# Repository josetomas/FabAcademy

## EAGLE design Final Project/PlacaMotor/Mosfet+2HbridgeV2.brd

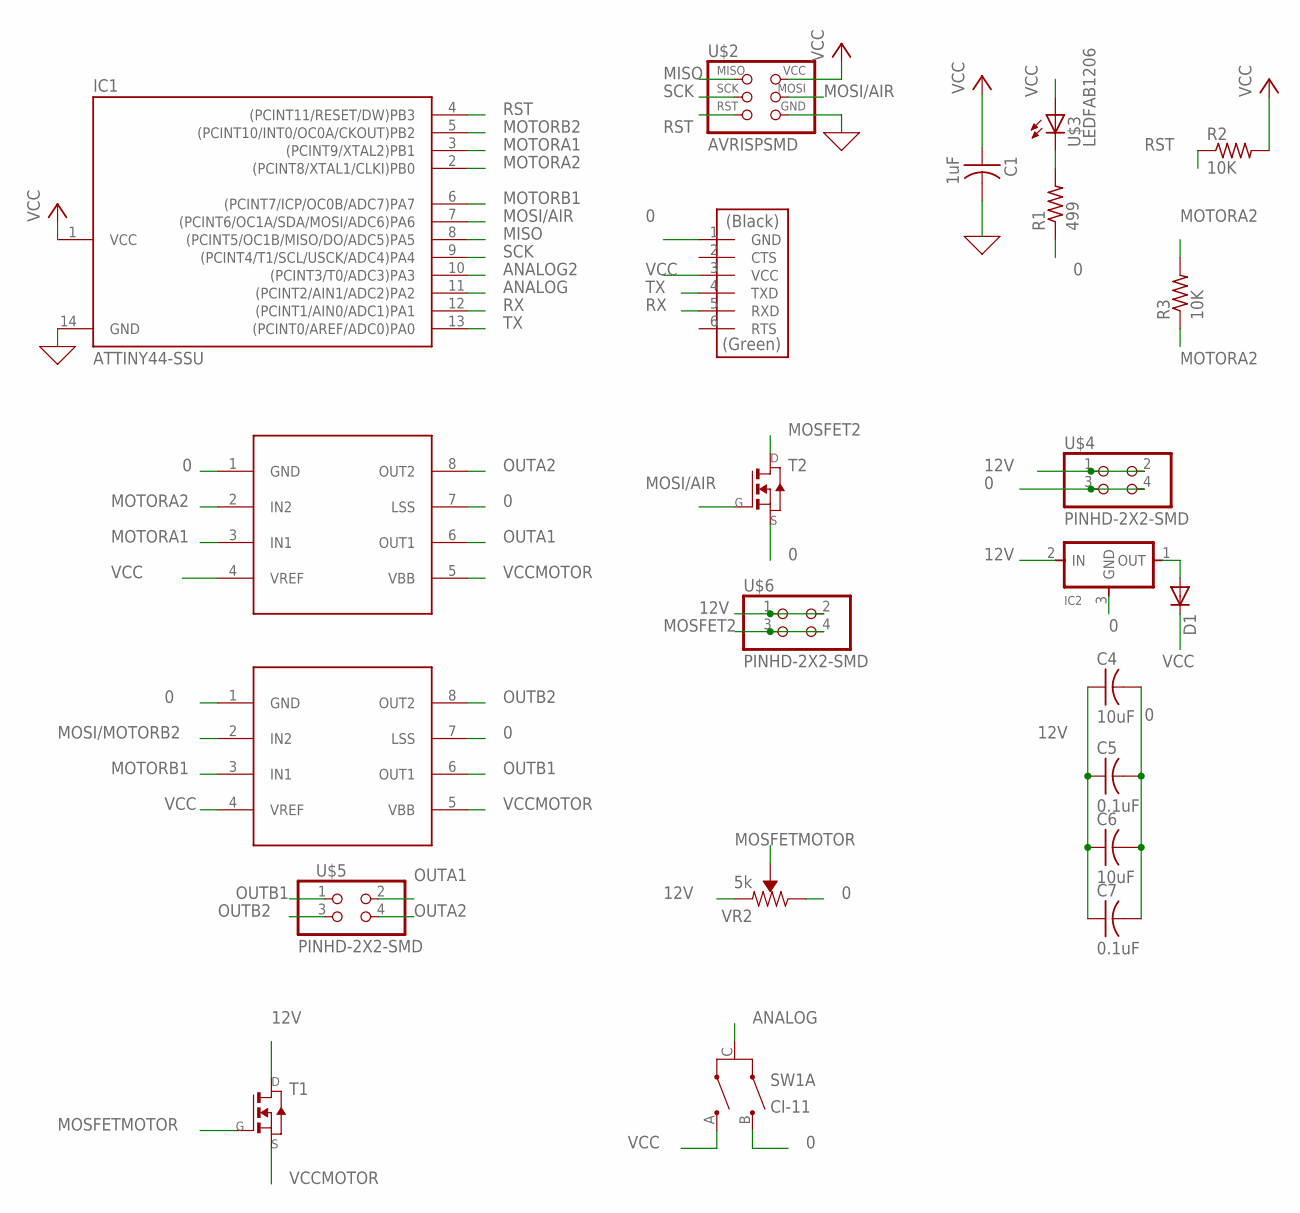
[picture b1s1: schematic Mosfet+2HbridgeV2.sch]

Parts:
C1: 1uF; C1206FAB
C4, C6: 10uF; C1206FAB
C5, C7: 0.1uF; C1206FAB
D1: DIODESOD123; SOD123
IC1: ATTINY44-SSU; SOIC14
IC2: REGULATORSOT23; SOT23
R1: 499; R1206FAB
R2, R3: 10K; R1206FAB
SW1: CI-11
T1, T2: NMOSFETSOT23; SOT-23
U$1: FTDI-SMD-HEADER; 1X06SMD
U$2: AVRISPSMD; 2X03SMD
U$3: LEDFAB1206; LED1206FAB
U$4, U$5, U$6: PINHD-2X2-SMD; 2X02SMD
U$7, U$8: A4953-H-BRIDGE-MOTOR-DRIVER; SOIC8
VR2: 5k; TRIMPOT-SMD-5MM

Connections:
0: C1.2, C4.2, C5.2, C6.2, C7.2, IC1.14 (GND), IC2.3 (GND), R1.1, SW1.B, T2.2 (S), U$1.1 (GND), U$2.6 (GND), U$4.3, U$4.4, U$7.1 (GND), U$7.7 (LSS), U$8.1 (GND), U$8.7 (LSS), VR2.C (CW)
12V: C4.1, C5.1, C6.1, C7.1, IC2.2 (IN), T1.1 (D), U$4.1, U$4.2, U$6.1, U$6.2, VR2.A (CCW)
ANALOG: IC1.11 ((PCINT2/AIN1/ADC2)PA2), SW1.C
ANALOG2: IC1.10 ((PCINT3/T0/ADC3)PA3)
MISO: IC1.8 ((PCINT5/OC1B/MISO/DO/ADC5)PA5), U$2.1 (MISO)
MOSFET2: T2.1 (D), U$6.3, U$6.4
MOSFETMOTOR: T1.3 (G), VR2.B (WIPER)
MOSI/AIR: IC1.7 ((PCINT6/OC1A/SDA/MOSI/ADC6)PA6), T2.3 (G), U$2.4 (MOSI)
MOSI/MOTORB2: U$7.2 (IN2)
MOTORA1: IC1.3 ((PCINT9/XTAL2)PB1), U$8.3 (IN1)
MOTORA2: IC1.2 ((PCINT8/XTAL1/CLKI)PB0), R3.1, R3.2, U$8.2 (IN2)
MOTORB1: IC1.6 ((PCINT7/ICP/OC0B/ADC7)PA7), U$7.3 (IN1)
MOTORB2: IC1.5 ((PCINT10/INT0/OC0A/CKOUT)PB2)
unnamed: R1.2, U$3.2 (C)
unnamed: D1.ANODE (A), IC2.1 (OUT)
OUTA1: U$5.2, U$8.6 (OUT1)
OUTA2: U$5.4, U$8.8 (OUT2)
OUTB1: U$5.1, U$7.6 (OUT1)
OUTB2: U$5.3, U$7.8 (OUT2)
RST: IC1.4 ((PCINT11/RESET/DW)PB3), R2.1, U$2.5 (RST)
RX: IC1.12 ((PCINT1/AIN0/ADC1)PA1), U$1.5 (RXD)
SCK: IC1.9 ((PCINT4/T1/SCL/USCK/ADC4)PA4), U$2.3 (SCK)
TX: IC1.13 ((PCINT0/AREF/ADC0)PA0), U$1.4 (TXD)
VCC: C1.1, D1.CATHODE (C), IC1.1 (VCC), R2.2, SW1.A, U$1.3 (VCC), U$2.2 (VCC), U$3.1 (A), U$7.4 (VREF), U$8.4 (VREF)
VCCMOTOR: T1.2 (S), U$7.5 (VBB), U$8.5 (VBB)

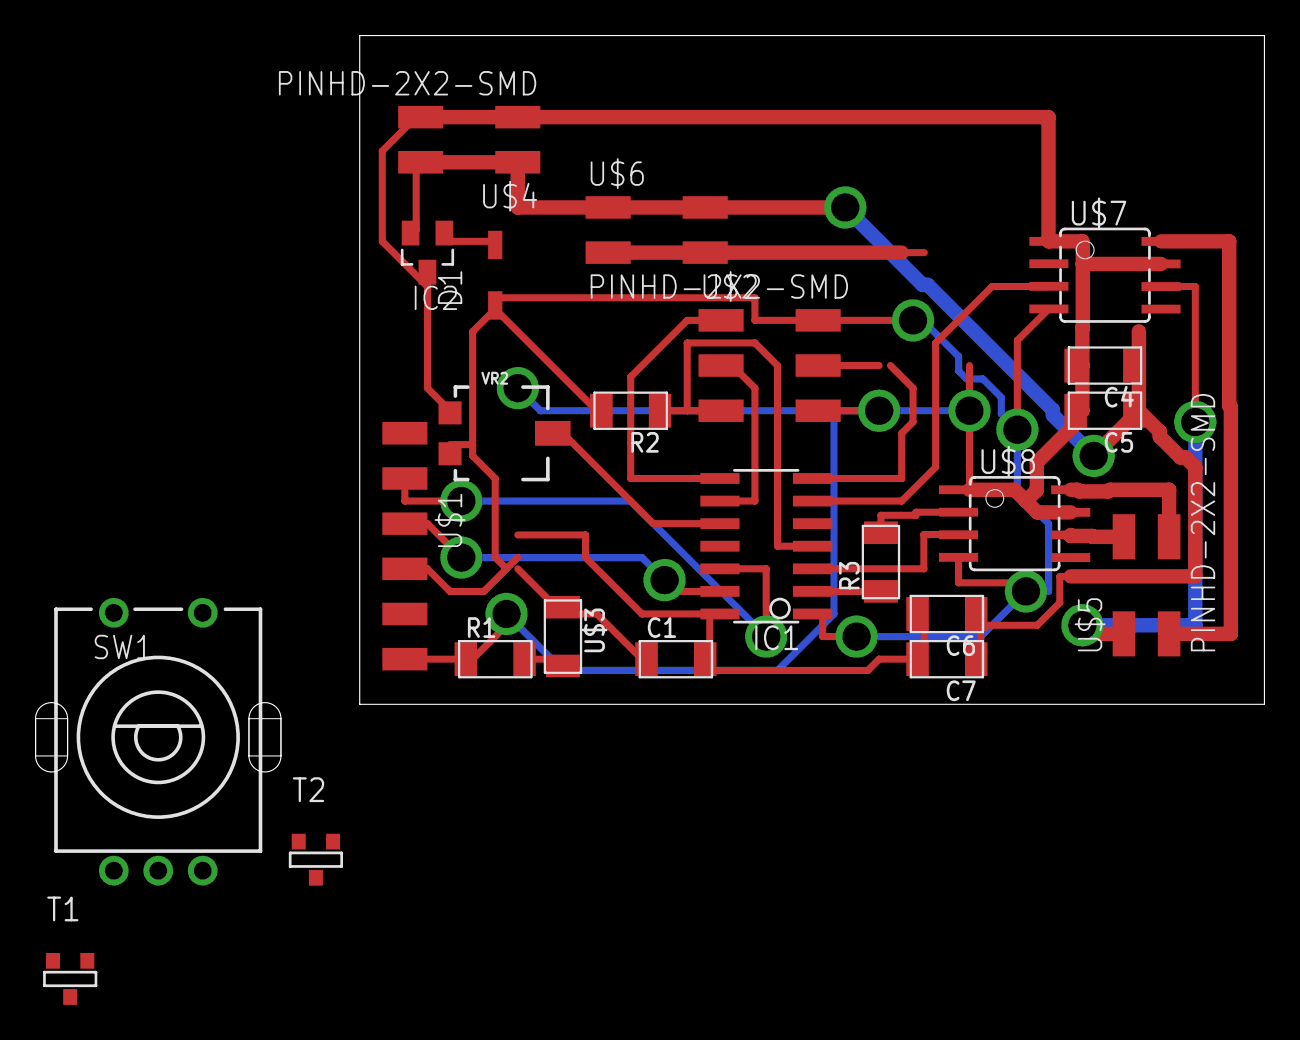
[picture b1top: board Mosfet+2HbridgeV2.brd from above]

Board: 2 copper layers, 50.9 x 37.6 mm, 23 parts (0 on the bottom side), 22 nets.

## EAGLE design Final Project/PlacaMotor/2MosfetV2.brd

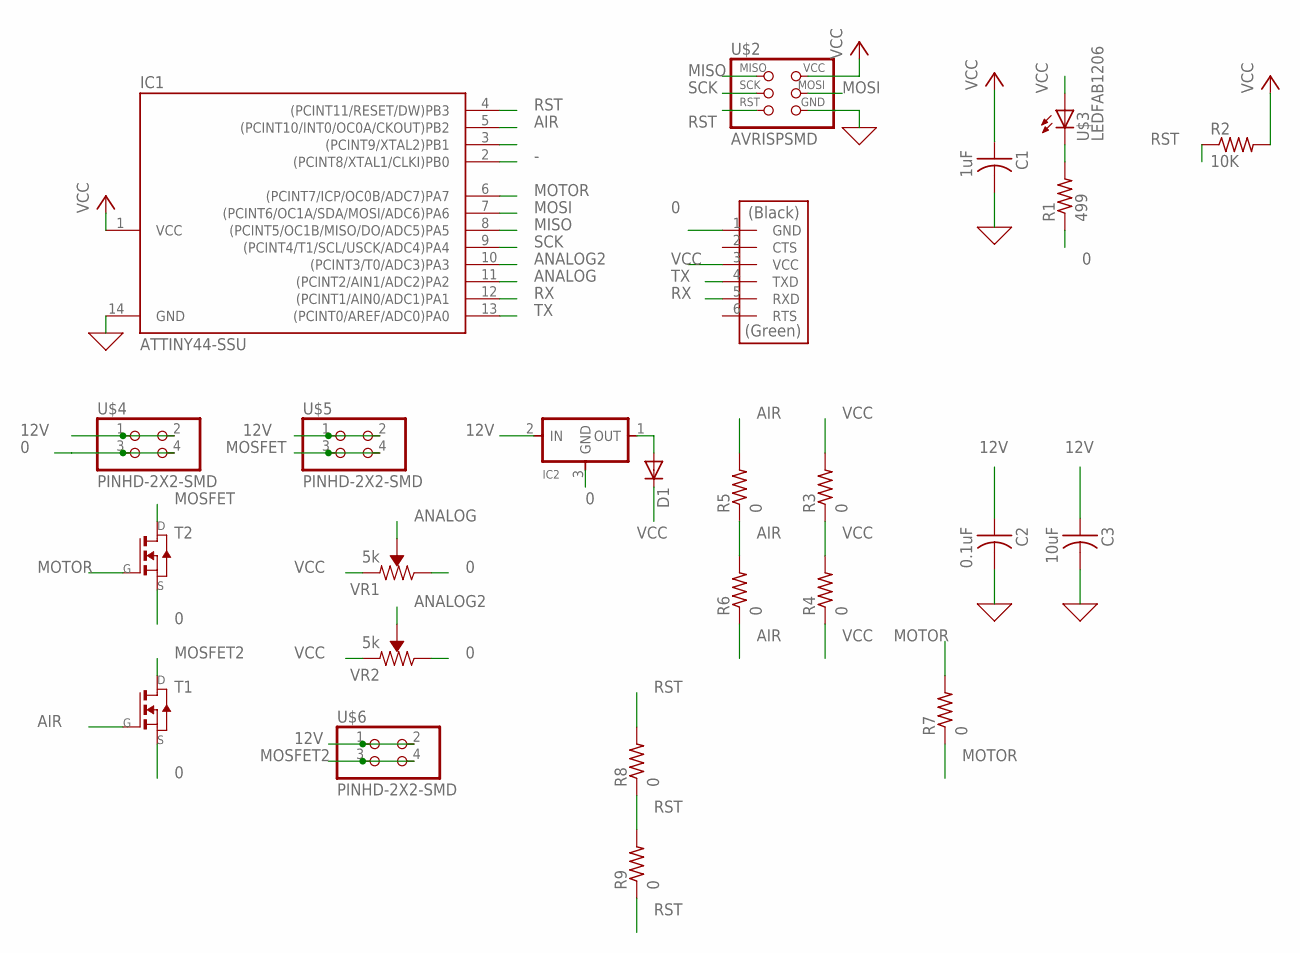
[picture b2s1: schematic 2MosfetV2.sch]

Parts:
C1: 1uF; C1206FAB
C2: 0.1uF; C1206FAB
C3: 10uF; C1206FAB
D1: DIODESOD123; SOD123
IC1: ATTINY44-SSU; SOIC14
IC2: REGULATORSOT23; SOT23
R1: 499; R1206FAB
R2: 10K; R1206FAB
R3, R4, R5, R6, R7, R8, R9: 0; R1206FAB
T1, T2: NMOSFETTO252; TO252
U$1: FTDI-SMD-HEADER; 1X06SMD
U$2: AVRISPSMD; 2X03SMD
U$3: LEDFAB1206; LED1206FAB
U$4, U$5, U$6: PINHD-2X2-SMD; 2X02SMD
VR1, VR2: 5k; TRIMPOT-SMD-5MM

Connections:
0: C1.2, C2.2, C3.2, IC1.14 (GND), IC2.3 (GND), R1.1, T1.2 (S), T2.2 (S), U$1.1 (GND), U$2.6 (GND), U$4.3, U$4.4, VR1.C (CW), VR2.C (CW)
12V: C2.1, C3.1, IC2.2 (IN), U$4.1, U$4.2, U$5.1, U$5.2, U$6.1, U$6.2
-: IC1.2 ((PCINT8/XTAL1/CLKI)PB0)
AIR: IC1.5 ((PCINT10/INT0/OC0A/CKOUT)PB2), R5.1, R5.2, R6.1, R6.2, T1.1 (G)
ANALOG: IC1.11 ((PCINT2/AIN1/ADC2)PA2), VR1.B (WIPER)
ANALOG2: IC1.10 ((PCINT3/T0/ADC3)PA3), VR2.B (WIPER)
MISO: IC1.8 ((PCINT5/OC1B/MISO/DO/ADC5)PA5), U$2.1 (MISO)
MOSFET: T2.3 (D), U$5.3, U$5.4
MOSFET2: T1.3 (D), U$6.3, U$6.4
MOSI: IC1.7 ((PCINT6/OC1A/SDA/MOSI/ADC6)PA6), U$2.4 (MOSI)
MOTOR: IC1.6 ((PCINT7/ICP/OC0B/ADC7)PA7), R7.1, R7.2, T2.1 (G)
unnamed: R1.2, U$3.2 (C)
unnamed: D1.ANODE (A), IC2.1 (OUT)
RST: IC1.4 ((PCINT11/RESET/DW)PB3), R2.1, R8.1, R8.2, R9.1, R9.2, U$2.5 (RST)
RX: IC1.12 ((PCINT1/AIN0/ADC1)PA1), U$1.5 (RXD)
SCK: IC1.9 ((PCINT4/T1/SCL/USCK/ADC4)PA4), U$2.3 (SCK)
TX: IC1.13 ((PCINT0/AREF/ADC0)PA0), U$1.4 (TXD)
VCC: C1.1, D1.CATHODE (C), IC1.1 (VCC), R2.2, R3.1, R3.2, R4.1, R4.2, U$1.3 (VCC), U$2.2 (VCC), U$3.1 (A), VR1.A (CCW), VR2.A (CCW)

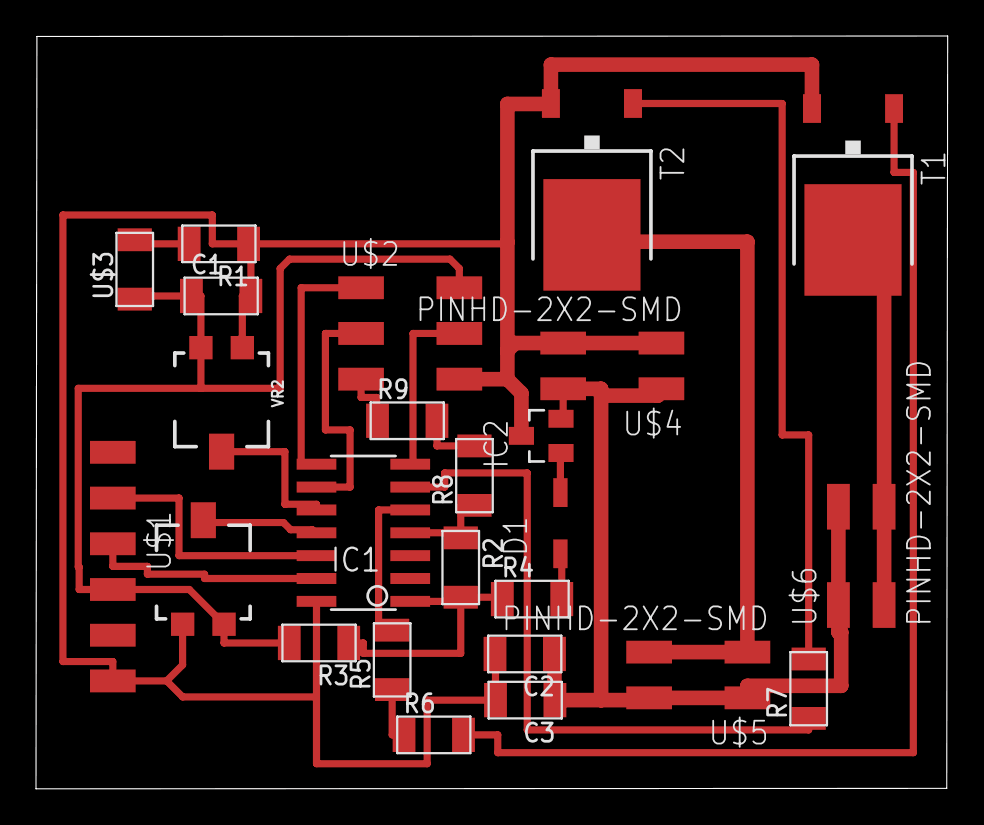
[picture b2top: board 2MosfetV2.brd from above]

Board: 2 copper layers, 50.6 x 41.8 mm, 25 parts (0 on the bottom side), 17 nets.

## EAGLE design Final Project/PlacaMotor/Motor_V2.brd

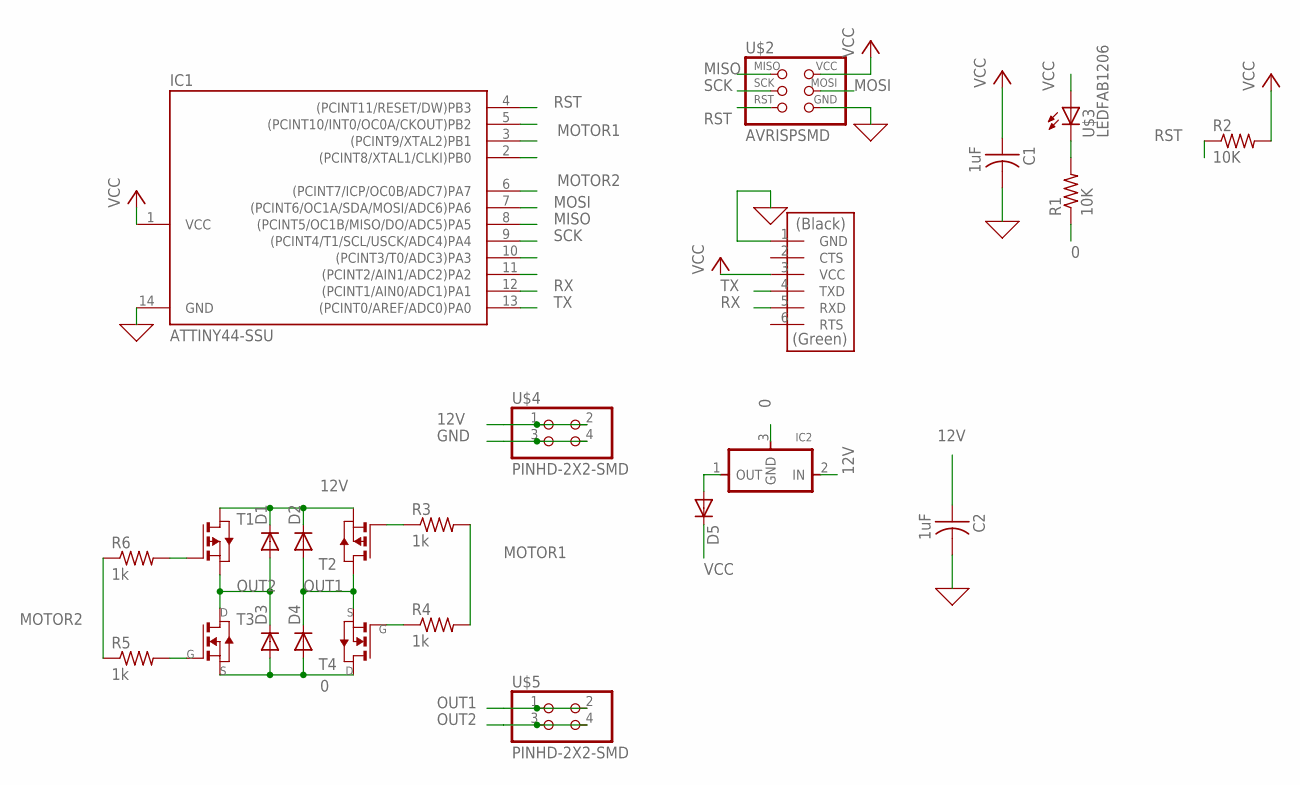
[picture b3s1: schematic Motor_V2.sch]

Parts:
C1, C2: 1uF; C1206FAB
D1, D2, D3, D4, D5: DIODESOD123; SOD123
IC1: ATTINY44-SSU; SOIC14
IC2: REGULATORSOT23; SOT23
R1, R2: 10K; R1206FAB
R3, R4, R5, R6: 1k; R1206FAB
T1, T2: PMOSFETSOT23; SOT-23
T3, T4: NMOSFETSOT23; SOT-23
U$1: FTDI-SMD-HEADER; 1X06SMD
U$2: AVRISPSMD; 2X03SMD
U$3: LEDFAB1206; LED1206FAB
U$4, U$5: PINHD-2X2-SMD; 2X02SMD

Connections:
0: C1.2, C2.2, D3.ANODE (A), D4.ANODE (A), IC1.14 (GND), IC2.3 (GND), R1.1, T3.2 (S), T4.1 (D), U$1.1 (GND), U$2.6 (GND)
12V: C2.1, D1.CATHODE (C), D2.CATHODE (C), IC2.2 (IN), T1.1 (D), T2.2 (S), U$4.1, U$4.2
GND: U$4.3, U$4.4
MISO: IC1.8 ((PCINT5/OC1B/MISO/DO/ADC5)PA5), U$2.1 (MISO)
MOSI: IC1.7 ((PCINT6/OC1A/SDA/MOSI/ADC6)PA6), U$2.4 (MOSI)
MOTOR1: IC1.5 ((PCINT10/INT0/OC0A/CKOUT)PB2), R3.2, R4.2
MOTOR2: IC1.6 ((PCINT7/ICP/OC0B/ADC7)PA7), R5.1, R6.1
unnamed: R1.2, U$3.2 (C)
unnamed: D5.ANODE (A), IC2.1 (OUT)
unnamed: R6.2, T1.3 (G)
unnamed: R5.2, T3.3 (G)
unnamed: R4.1, T4.3 (G)
unnamed: R3.1, T2.3 (G)
OUT1: D2.ANODE (A), D4.CATHODE (C), T2.1 (D), T4.2 (S), U$5.1, U$5.2
OUT2: D1.ANODE (A), D3.CATHODE (C), T1.2 (S), T3.1 (D), U$5.3, U$5.4
RST: IC1.4 ((PCINT11/RESET/DW)PB3), R2.1, U$2.5 (RST)
RX: IC1.12 ((PCINT1/AIN0/ADC1)PA1), U$1.5 (RXD)
SCK: IC1.9 ((PCINT4/T1/SCL/USCK/ADC4)PA4), U$2.3 (SCK)
TX: IC1.13 ((PCINT0/AREF/ADC0)PA0), U$1.4 (TXD)
VCC: C1.1, D5.CATHODE (C), IC1.1 (VCC), R2.2, U$1.3 (VCC), U$2.2 (VCC), U$3.1 (A)

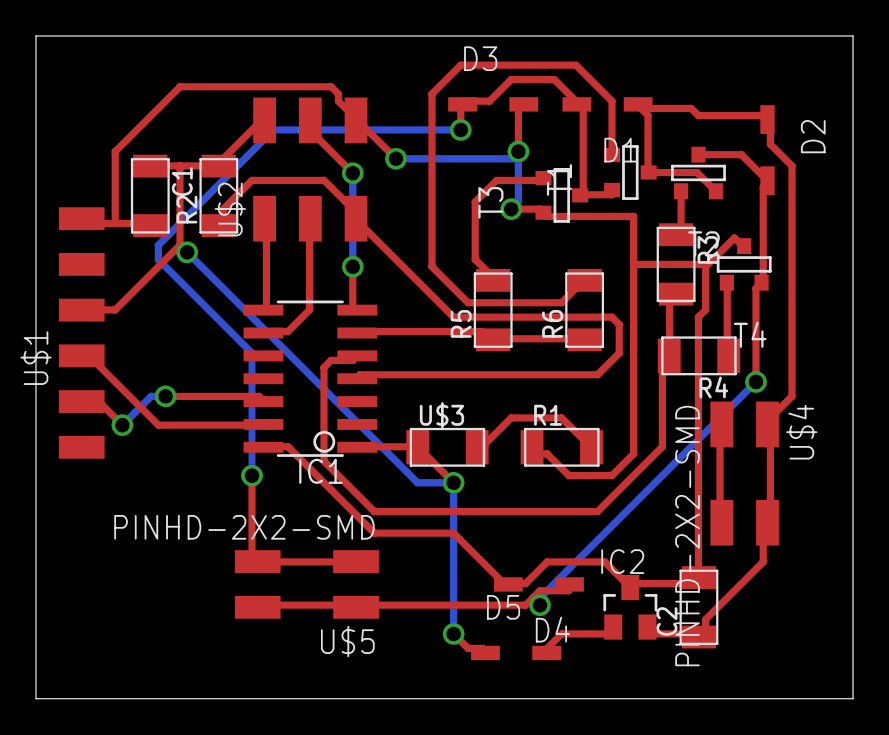
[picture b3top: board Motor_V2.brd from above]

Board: 2 copper layers, 45.4 x 36.8 mm, 24 parts (0 on the bottom side), 20 nets.

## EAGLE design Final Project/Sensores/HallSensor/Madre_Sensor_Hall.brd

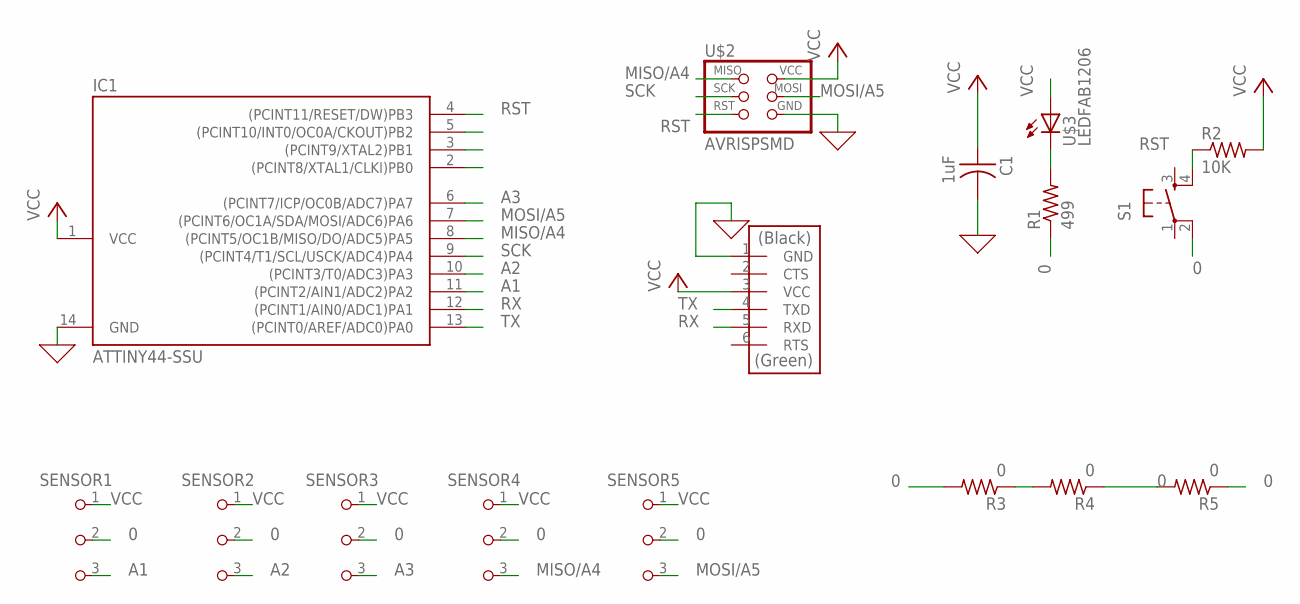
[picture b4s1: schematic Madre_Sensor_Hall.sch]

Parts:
C1: 1uF; C1206FAB
IC1: ATTINY44-SSU; SOIC14
R1: 499; R1206FAB
R2: 10K; R1206FAB
R3, R4, R5: 0; R1206FAB
S1: 6MM_SWITCH6MM_SWITCH; 6MM_SWITCH
SENSOR1, SENSOR2, SENSOR3, SENSOR4, SENSOR5: SPDTSWITCH
U$1: FTDI-SMD-HEADER; 1X06SMD
U$2: AVRISPSMD; 2X03SMD
U$3: LEDFAB1206; LED1206FAB

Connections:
0: C1.2, IC1.14 (GND), R1.1, R3.1, R3.2, R4.1, R4.2, R5.1, R5.2, S1.2 (P1), SENSOR1.2, SENSOR2.2, SENSOR3.2, SENSOR4.2, SENSOR5.2, U$1.1 (GND), U$2.6 (GND)
A1: IC1.11 ((PCINT2/AIN1/ADC2)PA2), SENSOR1.3
A2: IC1.10 ((PCINT3/T0/ADC3)PA3), SENSOR2.3
A3: IC1.6 ((PCINT7/ICP/OC0B/ADC7)PA7), SENSOR3.3
MISO/A4: IC1.8 ((PCINT5/OC1B/MISO/DO/ADC5)PA5), SENSOR4.3, U$2.1 (MISO)
MOSI/A5: IC1.7 ((PCINT6/OC1A/SDA/MOSI/ADC6)PA6), SENSOR5.3, U$2.4 (MOSI)
unnamed: R1.2, U$3.2 (C)
RST: IC1.4 ((PCINT11/RESET/DW)PB3), R2.1, S1.4 (S1), U$2.5 (RST)
RX: IC1.12 ((PCINT1/AIN0/ADC1)PA1), U$1.5 (RXD)
SCK: IC1.9 ((PCINT4/T1/SCL/USCK/ADC4)PA4), U$2.3 (SCK)
TX: IC1.13 ((PCINT0/AREF/ADC0)PA0), U$1.4 (TXD)
VCC: C1.1, IC1.1 (VCC), R2.2, SENSOR1.1, SENSOR2.1, SENSOR3.1, SENSOR4.1, SENSOR5.1, U$1.3 (VCC), U$2.2 (VCC), U$3.1 (A)

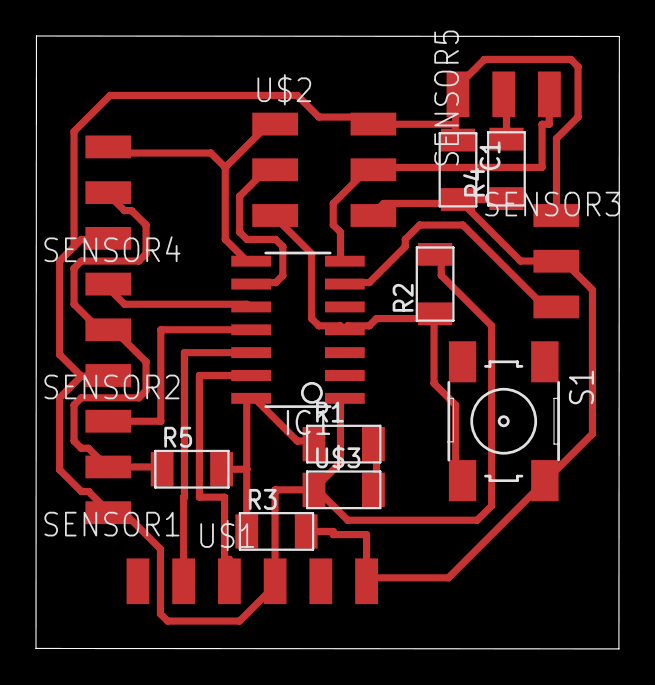
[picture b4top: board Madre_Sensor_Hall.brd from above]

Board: 2 copper layers, 32.4 x 34.1 mm, 16 parts (0 on the bottom side), 12 nets.

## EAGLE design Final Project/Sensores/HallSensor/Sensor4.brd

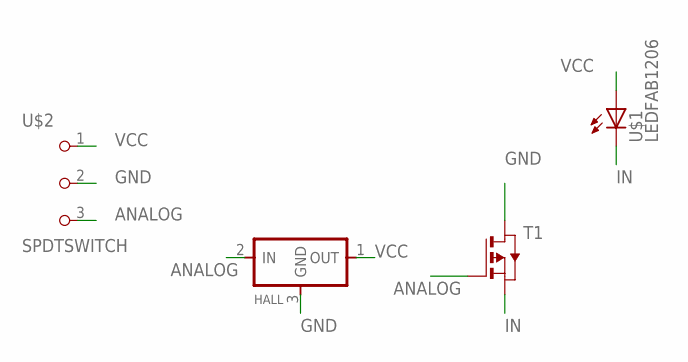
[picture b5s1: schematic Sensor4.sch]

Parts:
HALL: REGULATORSOT23; SOT23
T1: PMOSFETSOT23; SOT-23
U$1: LEDFAB1206; LED1206FAB
U$2: SPDTSWITCH

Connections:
ANALOG: HALL.2 (IN), T1.3 (G), U$2.3
GND: HALL.3 (GND), T1.1 (D), U$2.2
IN: T1.2 (S), U$1.2 (C)
VCC: HALL.1 (OUT), U$1.1 (A), U$2.1

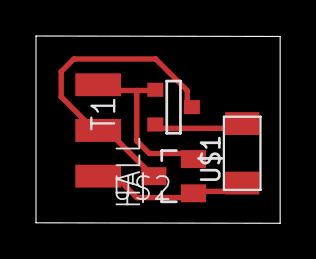
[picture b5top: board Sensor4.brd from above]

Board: 2 copper layers, 13.6 x 10.4 mm, 4 parts (0 on the bottom side), 4 nets.

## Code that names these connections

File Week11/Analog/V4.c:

#include <avr/io.h>
#include <util/delay.h>

#define output(directions,pin) (directions |= pin) // set port direction for output
#define set(port,pin) (port |= pin) // set port pin
#define clear(port,pin) (port &= (~pin)) // clear port pin
#define pin_test(pins,pin) (pins & pin) // test for port pin
#define bit_test(byte,bit) (byte & (1 << bit)) // test for bit set
#define bit_delay_time 102 // bit delay for 9600 with overhead
#define bit_delay() _delay_us(bit_delay_time) // RS232 bit delay
#define half_bit_delay() _delay_us(bit_delay_time/2) // RS232 half bit delay
#define charge_delay_1() _delay_us(1) // charge delay 1
#define charge_delay_2() _delay_us(10) // charge delay 2
#define charge_delay_3() _delay_us(100) // charge delay 3
#define settle_delay() _delay_us(100) // settle delay
#define char_delay() _delay_ms(10) // char delay

#define serial_port PORTA
#define serial_direction DDRA
#define serial_pin_out (1 << PA1)
#define charge_port PORTA
#define charge_direction DDRA
#define charge_pin1 (1 << PA7)
#define charge_pin2 (1 << PA5)
#define charge_pin3 (1<<PA4)


#define Sens1 0b00000011 //TX1@PA3
#define Sens2 0b00000010 //TX2@PA2
#define Sens3 0b00000000 //TX3@PA0

int Read_Sensor(uint8_t bit, unsigned char pin, unsigned char port){
	ADMUX |= bit;
	static unsigned char up_lo, up_hi, down_lo, down_hi;
	settle_delay();
   set(port, pin);
   charge_delay_1();
	ADCSRA |= (1<<ADSC);
	while (ADCSRA & (1<<ADSC))
      ;
   up_lo = ADCL;
   up_hi = ADCH;
   settle_delay();
   clear(port, pin);
   charge_delay_1();
   ADCSRA |= (1<<ADSC);
   while (ADCSRA & (1<<ADSC))
      ;
   down_lo = ADCL;
   down_hi = ADCH;

   int x = 256*up_hi+up_lo;
   int y=256*down_hi+down_lo;
   int z= x; 
   return z;

}

void put_char(volatile unsigned char *port, unsigned char pin, char txchar) {
   //
   // send character in txchar on port pin
   //    assumes line driver (inverts bits)
   //
   // start bit
   //
   clear(*port,pin);
   bit_delay();
   //
   // unrolled loop to write data bits
   //
   if bit_test(txchar,0)
      set(*port,pin);
   else
      clear(*port,pin);
   bit_delay();
   if bit_test(txchar,1)
      set(*port,pin);
   else
      clear(*port,pin);
   bit_delay();
   if bit_test(txchar,2)
      set(*port,pin);
   else
      clear(*port,pin);
   bit_delay();
   if bit_test(txchar,3)
      set(*port,pin);
   else
      clear(*port,pin);
   bit_delay();
   if bit_test(txchar,4)
      set(*port,pin);
   else
      clear(*port,pin);
   bit_delay();
   if bit_test(txchar,5)
      set(*port,pin);
   else
      clear(*port,pin);
   bit_delay();
   if bit_test(txchar,6)
      set(*port,pin);
   else
      clear(*port,pin);
   bit_delay();
   if bit_test(txchar,7)
      set(*port,pin);
   else
      clear(*port,pin);
   bit_delay();
   //
   // stop bit
   //
   set(*port,pin);
   bit_delay();
   //
   // char delay
   //
   bit_delay();
   }

int main (void){
 // Define clock devider
 CLKPR = (1<<CLKPCE);
 CLKPR = (0 << CLKPS3) | (0 << CLKPS2) | (0 << CLKPS1) | (0 << CLKPS0);

 //Set prescaler to 128
 ADCSRA = (1 << ADEN); // enable
 ADCSRA = (1<<ADEN)|(1<<ADPS2)|(1<<ADPS1)|(1<<ADPS0);
   // initialize output pins
   set(serial_port, serial_pin_out);
   output(serial_direction, serial_pin_out);

   DDRB = 0xFF;
   output(charge_direction, charge_pin1);
   output(charge_direction, charge_pin2);
   output(charge_direction, charge_pin3);
 
while(1){
   int z= Read_Sensor(Sens3,  charge_pin3, charge_port);
   if (z>200){
      PORTB &= ~(1<<PB2); //PORTx |=(the value<<number positions)
   }
   else{
      PORTB |= (1<<PB2); //PORTx |=(the value<<number positions)
   }
   int x= Read_Sensor(Sens2,  charge_pin2, charge_port);
   if (x>200){
      PORTB &= ~(1<<PB1); //PORTx |=(the value<<number positions)
   }
   else{
      PORTB |= (1<<PB1); //PORTx |=(the value<<number positions)
   }
	int y= Read_Sensor(Sens1,  charge_pin1, charge_port);
   if (y>200){
      PORTB &= ~(1<<PB0); //PORTx |=(the value<<number positions)
   }
   else{
      PORTB |= (1<<PB0); //PORTx |=(the value<<number positions)
   }
}
}

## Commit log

2019-03-04 no more problems
2019-03-05 windows
2019-03-15 codigo Week 6
2019-03-15 Inicio Semana 9
2019-03-16 Borrar Blink
2019-03-18 blink en C 1
2019-03-19 Makefile
2019-03-19 Week9 Final
2019-03-24 Calculos Final Projecto
2019-03-24 Week10
2019-03-26 Week10_VideoSimulation
2019-03-29 Week11
2019-04-01 la cague
2019-04-01 Codigo Analogo V1
2019-04-01 palca V1
2019-04-02 Board
2019-04-02 Avances
2019-04-03 Sensor otra versión
2019-04-03 Sensor Final
2019-04-08 coolterm
2019-04-10 Week12
2019-04-10 Hall Sensor
2019-04-11 Random
2019-04-12 Placa Motor
2019-04-12 MotorFail
2019-04-17 Thingiverse
2019-04-17 Stepper oK!
2019-04-18 Motor Stepper Final
2019-04-18 Stepper final final, este si!
2019-04-19 Bipolar Full
2019-04-19 Tiempo Motor
2019-04-19 delay
2019-04-20 Cambio sentido motor
2019-04-23 Pruebas Máquina con Arely
2019-04-29 Pruebas Impresión Materiales
2019-04-30 GCodes
2019-04-30 Networking boards
2019-04-30 pngs
2019-05-02 Atraso
2019-05-04 Gcode prueba Biomateriales
2019-05-05 Network master code
2019-05-05 weas bla bla
2019-05-09 Networking
2019-05-09 Ahora si porfa porfa
2019-05-14 Netowrking
2019-05-15 Placa Machine
2019-05-15 boards
2019-05-16 Machine Design
2019-05-16 slave
2019-05-16 master... la cague
2019-05-17 Networking finished
2019-05-24 Placa Ultrasonido
2019-05-24 Ruteo PCB
2019-05-25 Sensor
2019-05-25 Sensor ultrasonico
2019-05-26 fail :(
2019-05-26 Ulrasoni board 2
2019-05-26 Ultrasonic V2
2019-05-27 Ultrasonic Fail :(
2019-05-28 Chilipepper
2019-05-29 Sensores y mas sensores
2019-05-30 Codigo Prusa
2019-05-30 Sensor_Mosfet
2019-06-03 sensor hall imagenes
2019-06-03 imagenes placa motor
2019-06-03 Placa Motor V1
2019-06-04 placa motor2
2019-06-06 Pruebas Impresora + Rediseño placa con pistas mas grandes
2019-06-07 Placa FTDI
2019-06-10 Codigos G
2019-06-10 Placa Final plz
2019-06-14 Week14 ok
2019-06-27 lala
2019-07-03 Placas

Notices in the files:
parts and their libraries:
SparkFun-Resistors: Licensing: Creative Commons ShareAlike 4.0 International - https://creativecommons.org/licenses/by-sa/4.0
